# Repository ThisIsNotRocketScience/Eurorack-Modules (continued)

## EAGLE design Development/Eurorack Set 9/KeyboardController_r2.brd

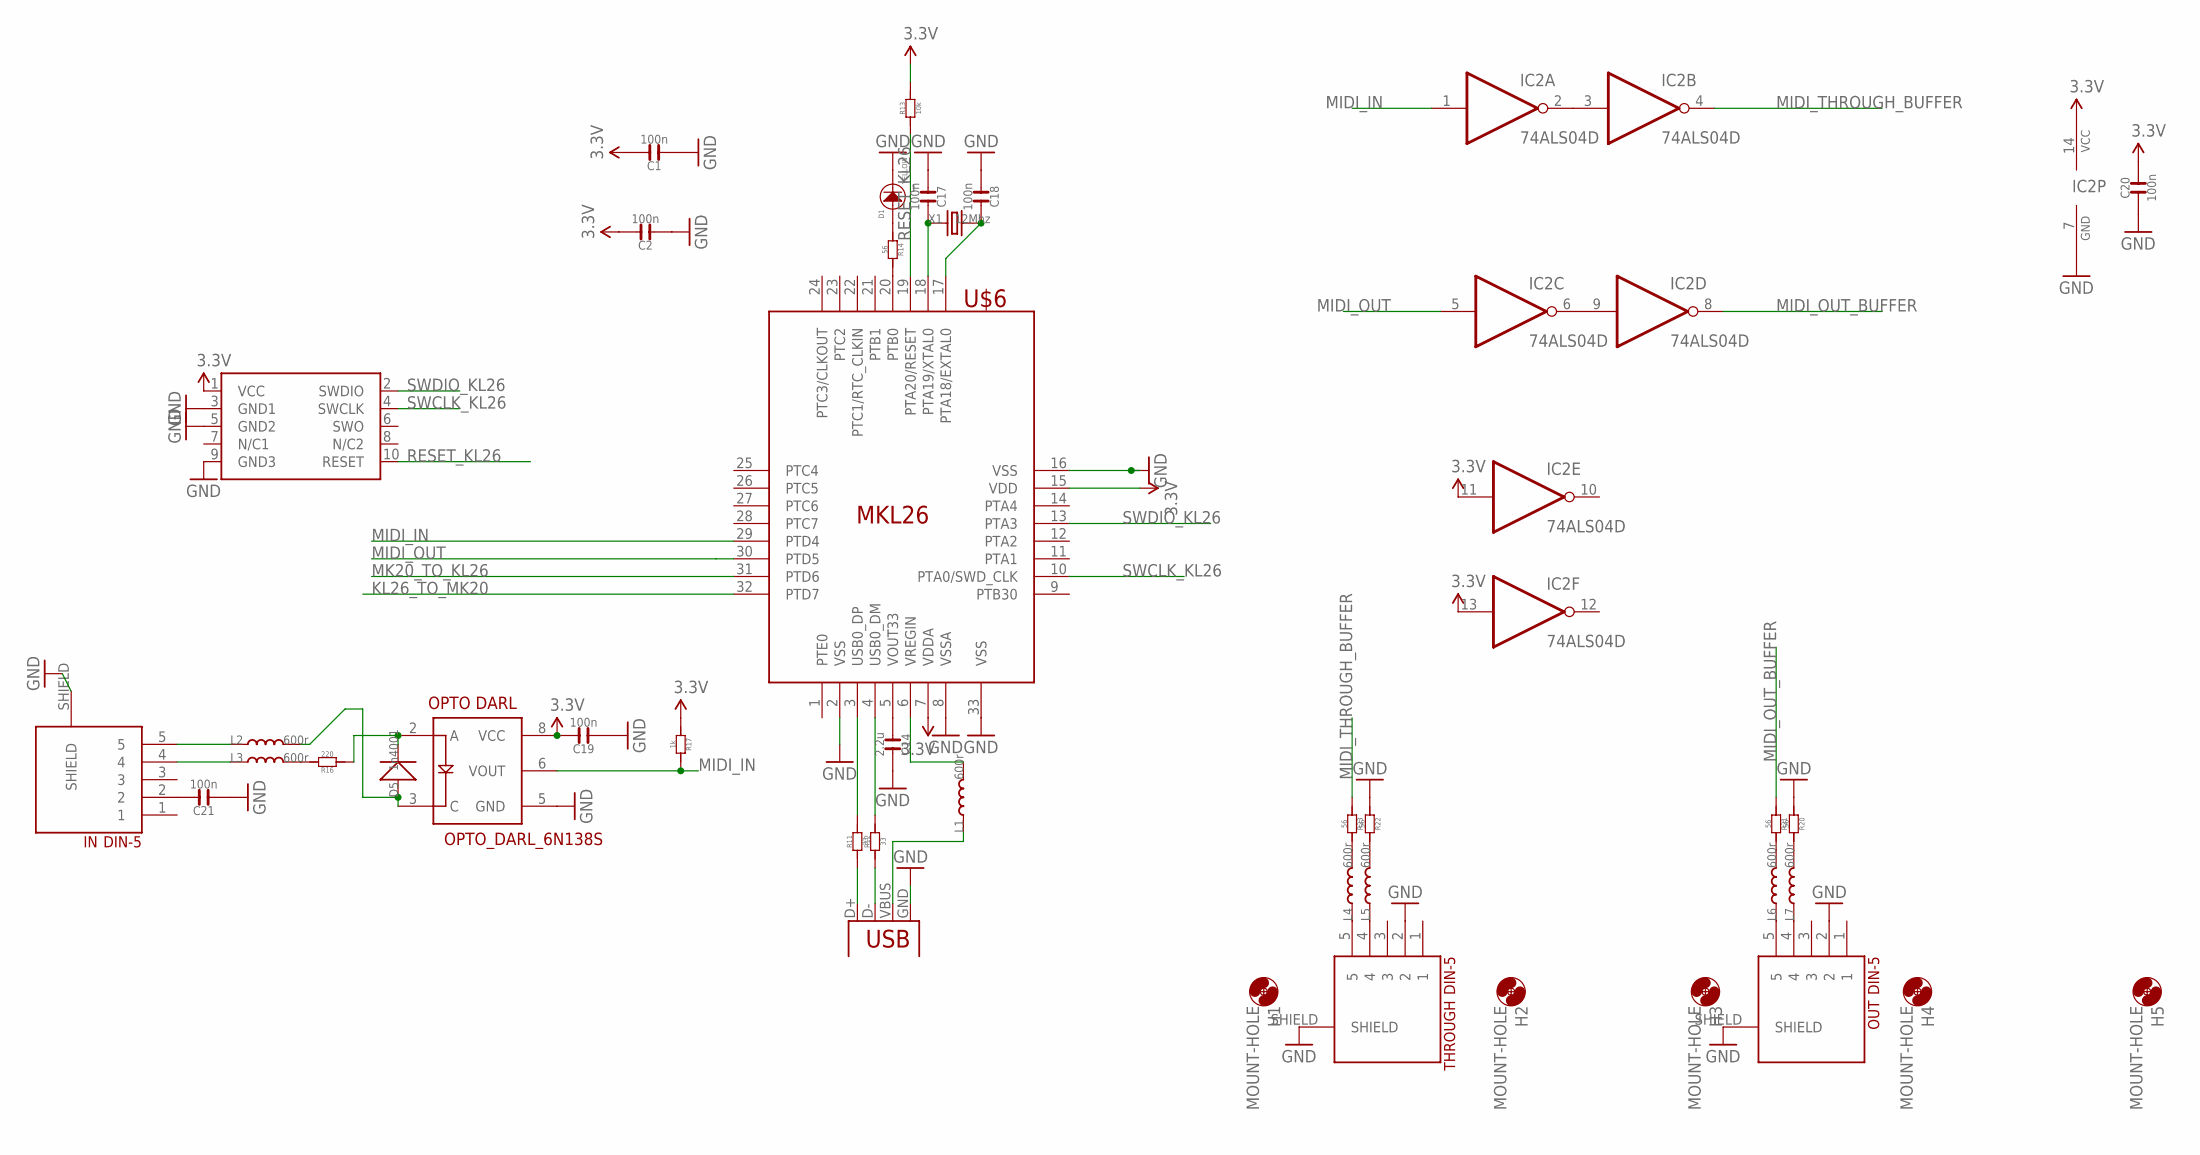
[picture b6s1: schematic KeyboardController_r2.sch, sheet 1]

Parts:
C1, C2, C17, C18, C19, C20, C21: 100n; C0603
C14: 2.2u; C0603
D1: YELLOW; LED0603
D5: 1n4001; SOD123
H1, H2, H3, H4, H5: MOUNT-HOLE; 3.2-NOMARKINGS-SMALLSAFEZONE
IC2: 74ALS04D; SO14
IN: DIN-5; DIN-5-VERTICAL
L1, L2, L3, L4, L5, L6, L7: 600r; L0603
OUT: DIN-5; DIN-5-VERTICAL
R11, R12: 33; R0603
R13: 10k; R0603
R14, R20, R21, R22, R23: 56; R0603
R16: 220; R0603
R17: 1k; R0603
SWD2: CORTEX_SWD; M50-3600542
THROUGH: DIN-5; DIN-5-VERTICAL
U$6: MKL26; QFN50P500X500X90-33N
U$9: OPTO_DARL_6N138S; 8-SMD
USB: USBVERTICAL_CENTERED; USB-B-PTH-VERTICAL-CENTERED
X1: 12Mhz; 2P-SMD-5.0X3.2

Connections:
3.3V: C1.2, C2.2, C19.2, C20.2, IC2.11 (I), IC2.13 (I), IC2.14 (VCC), R13.2, R17.1, SWD2.1 (VCC), U$6.7 (VDDA), U$6.15 (VDD), U$9.8 (VCC); also elsewhere on the board
GND: C1.1, C2.1, C14.2, C17.1, C18.1, C19.1, C20.1, C21.1, D1.-, IC2.7 (GND), IN.SHIELD, OUT.2, OUT.SHIELD, R20.1, R22.1, SWD2.3 (GND1), SWD2.5 (GND2), SWD2.9 (GND3), THROUGH.2, THROUGH.SHIELD, U$6.2 (VSS), U$6.8 (VSSA), U$6.16 (VSS), U$6.33 (VSS), U$9.5 (GND), USB.GND; also elsewhere on the board
KL26_TO_MK20: U$6.32 (PTD7); also elsewhere on the board
MIDI_IN: IC2.1 (I), R17.2, U$6.29 (PTD4), U$9.6 (VOUT)
MIDI_OUT: IC2.5 (I), U$6.30 (PTD5)
MIDI_OUT_BUFFER: IC2.8 (O), R21.1
MIDI_THROUGH_BUFFER: IC2.4 (O), R23.1
MK20_TO_KL26: U$6.31 (PTD6); also elsewhere on the board
unnamed: R11.2, U$6.3 (USB0_DP)
unnamed: R12.2, U$6.4 (USB0_DM)
unnamed: R14.2, U$6.20 (PTB0)
unnamed: D1.+, R14.1
unnamed: C14.1, U$6.5 (VOUT33)
unnamed: R11.1, USB.D+
unnamed: R12.1, USB.D-
unnamed: L1.1, USB.VBUS
unnamed: L1.2, U$6.6 (VREGIN)
unnamed: C17.2, U$6.18 (PTA19/XTAL0), X1.1
unnamed: C18.2, U$6.17 (PTA18/EXTAL0), X1.2
unnamed: IN.5, L2.1
unnamed: IN.4, L3.1
unnamed: L4.1, THROUGH.5
unnamed: L5.1, THROUGH.4
unnamed: L6.1, OUT.5
unnamed: L7.1, OUT.4
unnamed: D5.-, R16.1, U$9.2 (A)
unnamed: D5.+, L2.2, U$9.3 (C)
unnamed: L3.2, R16.2
unnamed: IC2.2 (O), IC2.3 (I)
unnamed: IC2.6 (O), IC2.9 (I)
unnamed: C21.2, IN.2
unnamed: L7.2, R20.2
unnamed: L6.2, R21.2
unnamed: L5.2, R22.2
unnamed: L4.2, R23.2
RESET_KL26: R13.1, SWD2.10 (RESET), U$6.19 (PTA20/RESET)
SWCLK_KL26: SWD2.4 (SWCLK), U$6.10 (PTA0/SWD_CLK)
SWDIO_KL26: SWD2.2 (SWDIO), U$6.13 (PTA3)

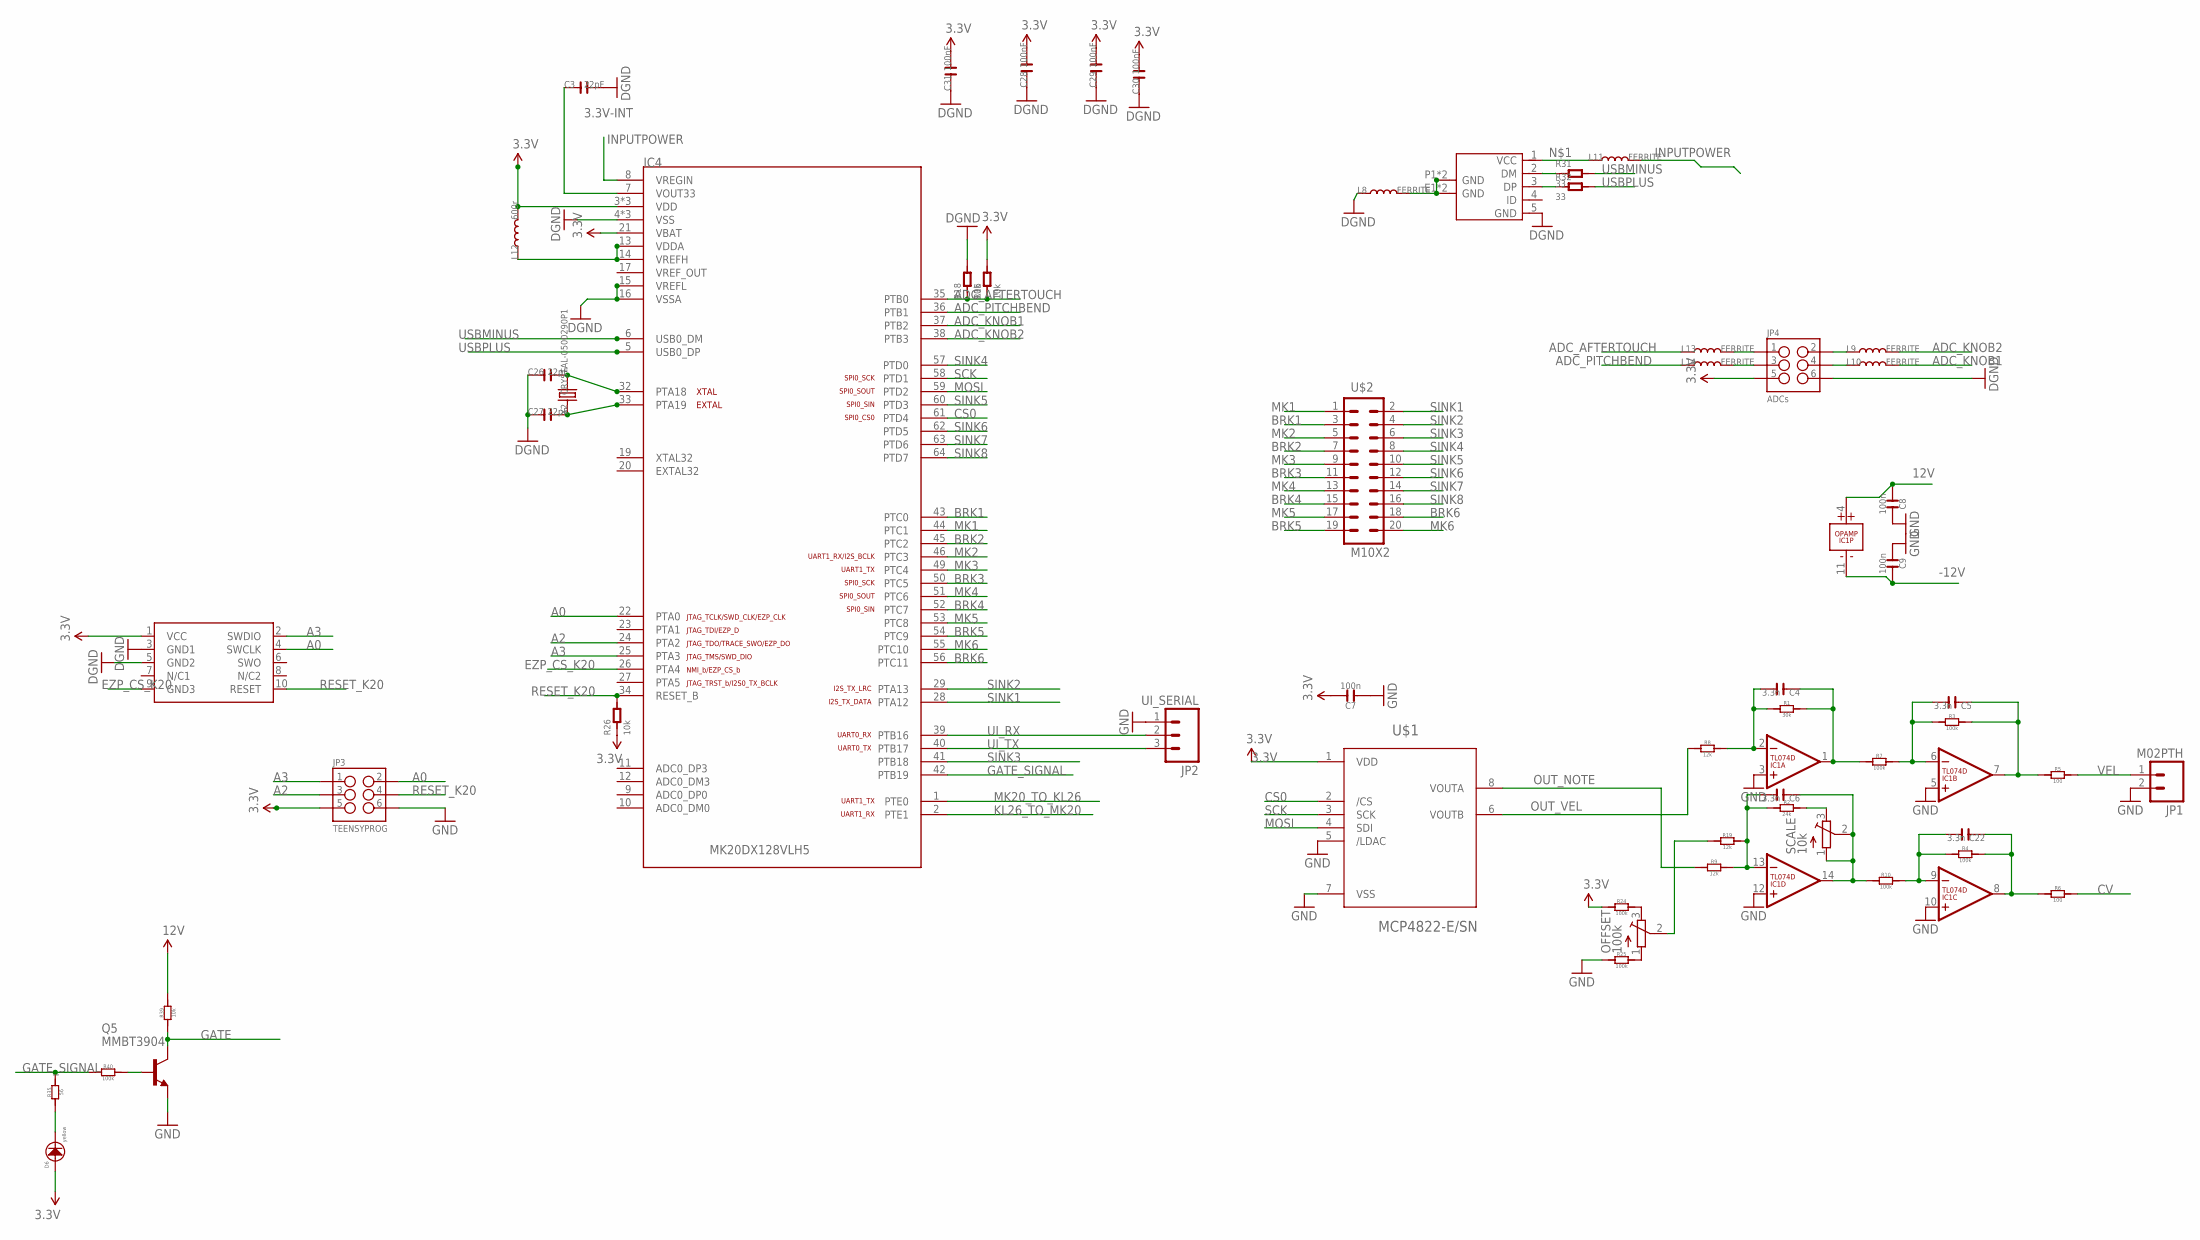
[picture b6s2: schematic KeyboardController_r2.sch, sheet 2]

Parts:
C3, C26, C27: 22pF; C0603
C4, C5, C6, C22: 3.3n; C0603
C7, C8, C9: 100n; C0603
C28, C29, C30, C31: 100nF; C0603
D6: yellow; LED0603
IC1: TL074D; SO14
IC4: MK20DX128VLH5
J2: MICRO-USB-5P-340015001; B-SMD-5P
JP1: M02PTH; 1X02
JP2: UI_SERIAL; 1X03
JP3: TEENSYPROG; 2X3-SHROUDED
JP4: ADCs; 2X3-SHROUDED
L8, L9, L10, L11, L13, L14: FERRITE; L0603
L12: 600r; L0603
OFFSET: 100k; TC33X
Q5: MMBT3904; SOT23-BEC; MPN PMBT3904,215
R1: 30k; R0603
R2: 24k; R0603
R3, R4, R7, R10, R24, R25, R40: 100k; R0603
R5, R6: 100; R0603
R8, R9, R19: 12k; R0603
R15, R18, R26, R39: 10k; R0603
R31, R32: 33; R0603
R35: 56; R0603
SCALE: 10k; TC33X
SWD1: CORTEX_SWD; M50-3600542
U$1: MCP4822-E/SN; SOIC8-N_MC
U$2: M10X2; 2X10
X2: CRYSTAL-0500290P1; 2P-SMD-5.0X3.2

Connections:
3.3V: C7.2, C28.2, C29.2, C30.2, C31.2, D6.+, IC4.3 (VDD), IC4.21 (VBAT), IC4.30 (VDD), IC4.48 (VDD), JP3.5, JP4.5, L12.2, R15.2, R24.1, R26.1, SWD1.1 (VCC), U$1.1 (VDD); also elsewhere on the board
3.3V-INT: C3.1, IC4.7 (VOUT33)
12V: C8.1, IC1.4 (V+), R39.2; also elsewhere on the board
-12V: C9.2, IC1.11 (V-); also elsewhere on the board
A0: IC4.22 (PTA0), JP3.2, SWD1.4 (SWCLK)
A2: IC4.24 (PTA2), JP3.3
A3: IC4.25 (PTA3), JP3.1, SWD1.2 (SWDIO)
ADC_AFTERTOUCH: IC4.35 (PTB0), L13.1, R15.1, R18.1
ADC_KNOB1: IC4.37 (PTB2), L10.2
ADC_KNOB2: IC4.38 (PTB3), L9.2
ADC_PITCHBEND: IC4.36 (PTB1), L14.1
BRK1: IC4.43 (PTC0), U$2.3
BRK2: IC4.45 (PTC2), U$2.7
BRK3: IC4.50 (PTC5), U$2.11
BRK4: IC4.52 (PTC7), U$2.15
BRK5: IC4.54 (PTC9), U$2.19
BRK6: IC4.56 (PTC11), U$2.18
CS0: IC4.61 (PTD4), U$1.2 (/CS)
CV: R6.2; also elsewhere on the board
EZP_CS_K20: IC4.26 (PTA4), SWD1.9 (GND3)
GATE: Q5.C, R39.1; also elsewhere on the board
GATE_SIGNAL: IC4.42 (PTB19), R35.2, R40.1
GND: C3.2, C7.1, C8.2, C9.1, C26.1, C27.1, C28.1, C29.1, C30.1, C31.1, IC1.3 (+IN), IC1.5 (+IN), IC1.10 (+IN), IC1.12 (+IN), IC4.4 (VSS), IC4.15 (VREFL), IC4.16 (VSSA), IC4.31 (VSS), IC4.47 (VSS), J2.5 (GND), JP1.2, JP2.1, JP3.6, JP4.6, L8.1, Q5.E, R18.2, R25.1, SWD1.3 (GND1), SWD1.5 (GND2), U$1.5 (/LDAC), U$1.7 (VSS); also elsewhere on the board
INPUTPOWER: IC4.8 (VREGIN), L11.2
KL26_TO_MK20: IC4.2 (PTE1); also elsewhere on the board
MK1: IC4.44 (PTC1), U$2.1
MK2: IC4.46 (PTC3), U$2.5
MK3: IC4.49 (PTC4), U$2.9
MK4: IC4.51 (PTC6), U$2.13
MK5: IC4.53 (PTC8), U$2.17
MK6: IC4.55 (PTC10), U$2.20
MK20_TO_KL26: IC4.1 (PTE0); also elsewhere on the board
MOSI: IC4.59 (PTD2), U$1.4 (SDI)
unnamed: J2.1 (VCC), L11.1
unnamed: R2.2, SCALE.3 (E)
unnamed: J2.2 (DM), R31.1
unnamed: J2.3 (DP), R32.1
unnamed: J2.E1 (GND), J2.E2 (GND), J2.P1 (GND), J2.P2 (GND), L8.2
unnamed: C26.2, IC4.32 (PTA18), X2.2
unnamed: C27.2, IC4.33 (PTA19), X2.1
unnamed: C4.2, IC1.2 (-IN), R1.1, R8.2
unnamed: C4.1, IC1.1 (OUT), R1.2, R7.1
unnamed: C5.2, IC1.6 (-IN), R3.1, R7.2
unnamed: C5.1, IC1.7 (OUT), R3.2, R5.1
unnamed: C6.2, IC1.13 (-IN), R2.1, R9.2, R19.2
unnamed: C6.1, IC1.14 (OUT), R10.1, SCALE.1 (A), SCALE.2 (S)
unnamed: C22.2, IC1.9 (-IN), R4.1, R10.2
unnamed: C22.1, IC1.8 (OUT), R4.2, R6.1
unnamed: JP4.2, L9.1
unnamed: IC4.13 (VDDA), IC4.14 (VREFH), L12.1
unnamed: D6.-, R35.1
unnamed: OFFSET.2 (S), R19.1
unnamed: OFFSET.3 (E), R24.2
unnamed: OFFSET.1 (A), R25.2
unnamed: JP4.4, L10.1
unnamed: JP4.1, L13.2
unnamed: JP4.3, L14.2
unnamed: Q5.B, R40.2
OUT_NOTE: R9.1, U$1.8 (VOUTA)
OUT_VEL: R8.1, U$1.6 (VOUTB)
RESET_K20: IC4.34 (RESET_B), JP3.4, R26.2, SWD1.10 (RESET)
SCK: IC4.58 (PTD1), U$1.3 (SCK)
SINK1: IC4.28 (PTA12), U$2.2
SINK2: IC4.29 (PTA13), U$2.4
SINK3: IC4.41 (PTB18), U$2.6
SINK4: IC4.57 (PTD0), U$2.8
SINK5: IC4.60 (PTD3), U$2.10
SINK6: IC4.62 (PTD5), U$2.12
SINK7: IC4.63 (PTD6), U$2.14
SINK8: IC4.64 (PTD7), U$2.16
UI_RX: IC4.39 (PTB16), JP2.2
UI_TX: IC4.40 (PTB17), JP2.3
USBMINUS: IC4.6 (USB0_DM), R31.2
USBPLUS: IC4.5 (USB0_DP), R32.2
VEL: JP1.1, R5.2

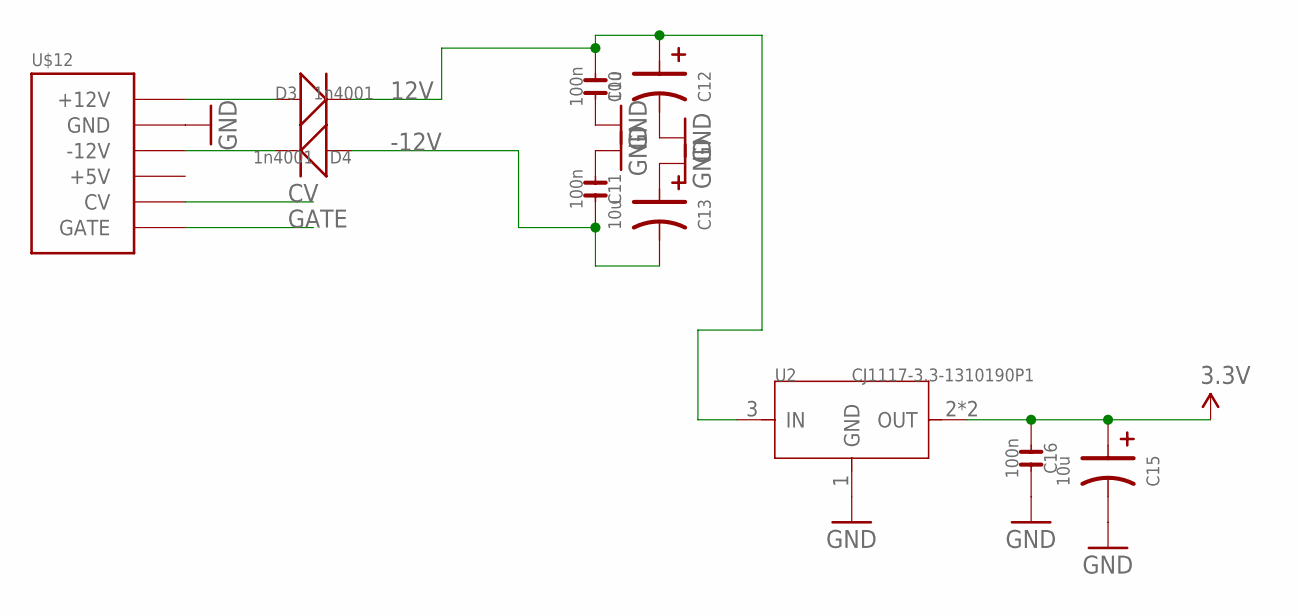
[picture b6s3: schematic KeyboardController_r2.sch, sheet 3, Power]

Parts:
C10, C11, C16: 100n; C0603
C12, C13, C15: 10u; CASE-A_3216
D3, D4: 1n4001; SOD123
U2: CJ1117-3.3-1310190P1; SOT223
U$12: POWER_SHROUDED_NOTEXT; POWER_16_SHROUDED_NOTEXT

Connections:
3.3V: C15.+ (1), C16.1, U2.2 (OUT), U2.TER (OUT); also elsewhere on the board
12V: C10.1, C12.+ (1), D3.-, U2.3 (IN); also elsewhere on the board
12VIN: D3.+, U$12.9 (+12V), U$12.10 (+12V)
-12V: C11.2, C13.- (2), D4.+; also elsewhere on the board
-12VIN: D4.-, U$12.1 (-12V), U$12.2 (-12V)
CV: U$12.13 (CV), U$12.14 (CV); also elsewhere on the board
GATE: U$12.15 (GATE), U$12.16 (GATE); also elsewhere on the board
GND: C10.2, C11.1, C12.- (2), C13.+ (1), C15.- (2), C16.2, U2.1 (GND), U$12.3 (GND), U$12.4 (GND), U$12.5 (GND), U$12.6 (GND), U$12.7 (GND), U$12.8 (GND); also elsewhere on the board

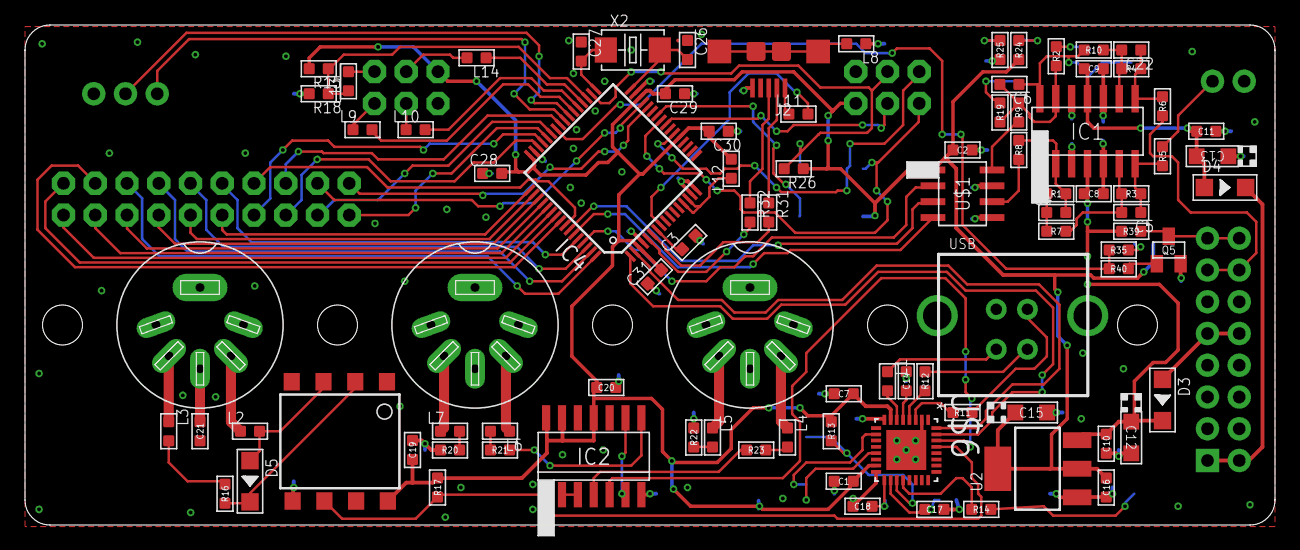
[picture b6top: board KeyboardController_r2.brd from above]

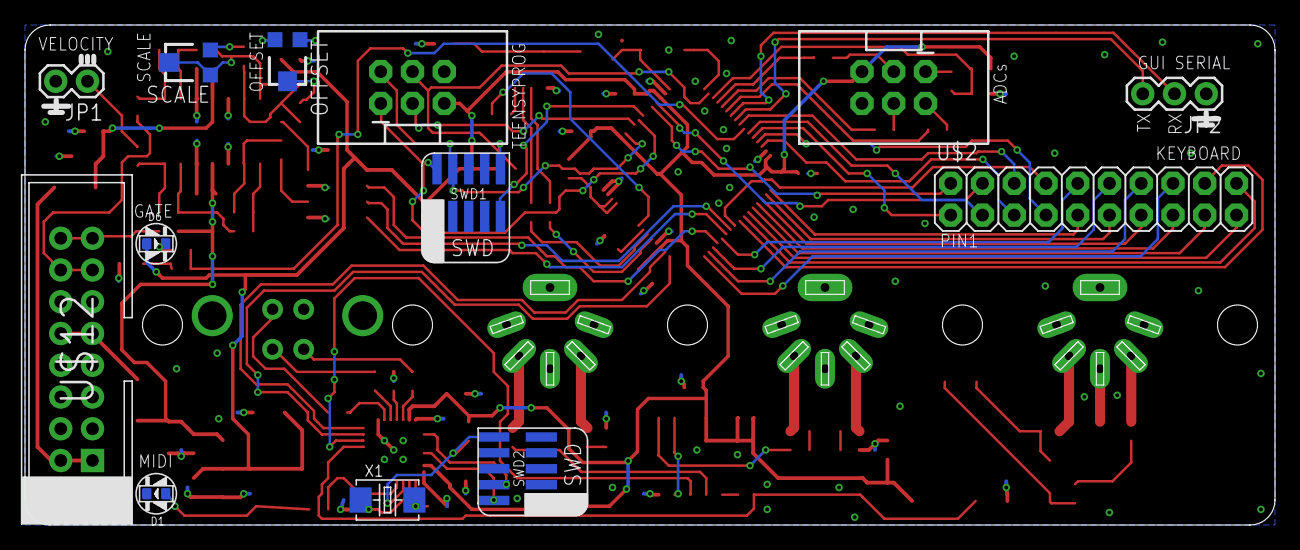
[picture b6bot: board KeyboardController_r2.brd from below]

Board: 2 copper layers, 100.0 x 40.0 mm, 108 parts (13 on the bottom side), 111 nets.
